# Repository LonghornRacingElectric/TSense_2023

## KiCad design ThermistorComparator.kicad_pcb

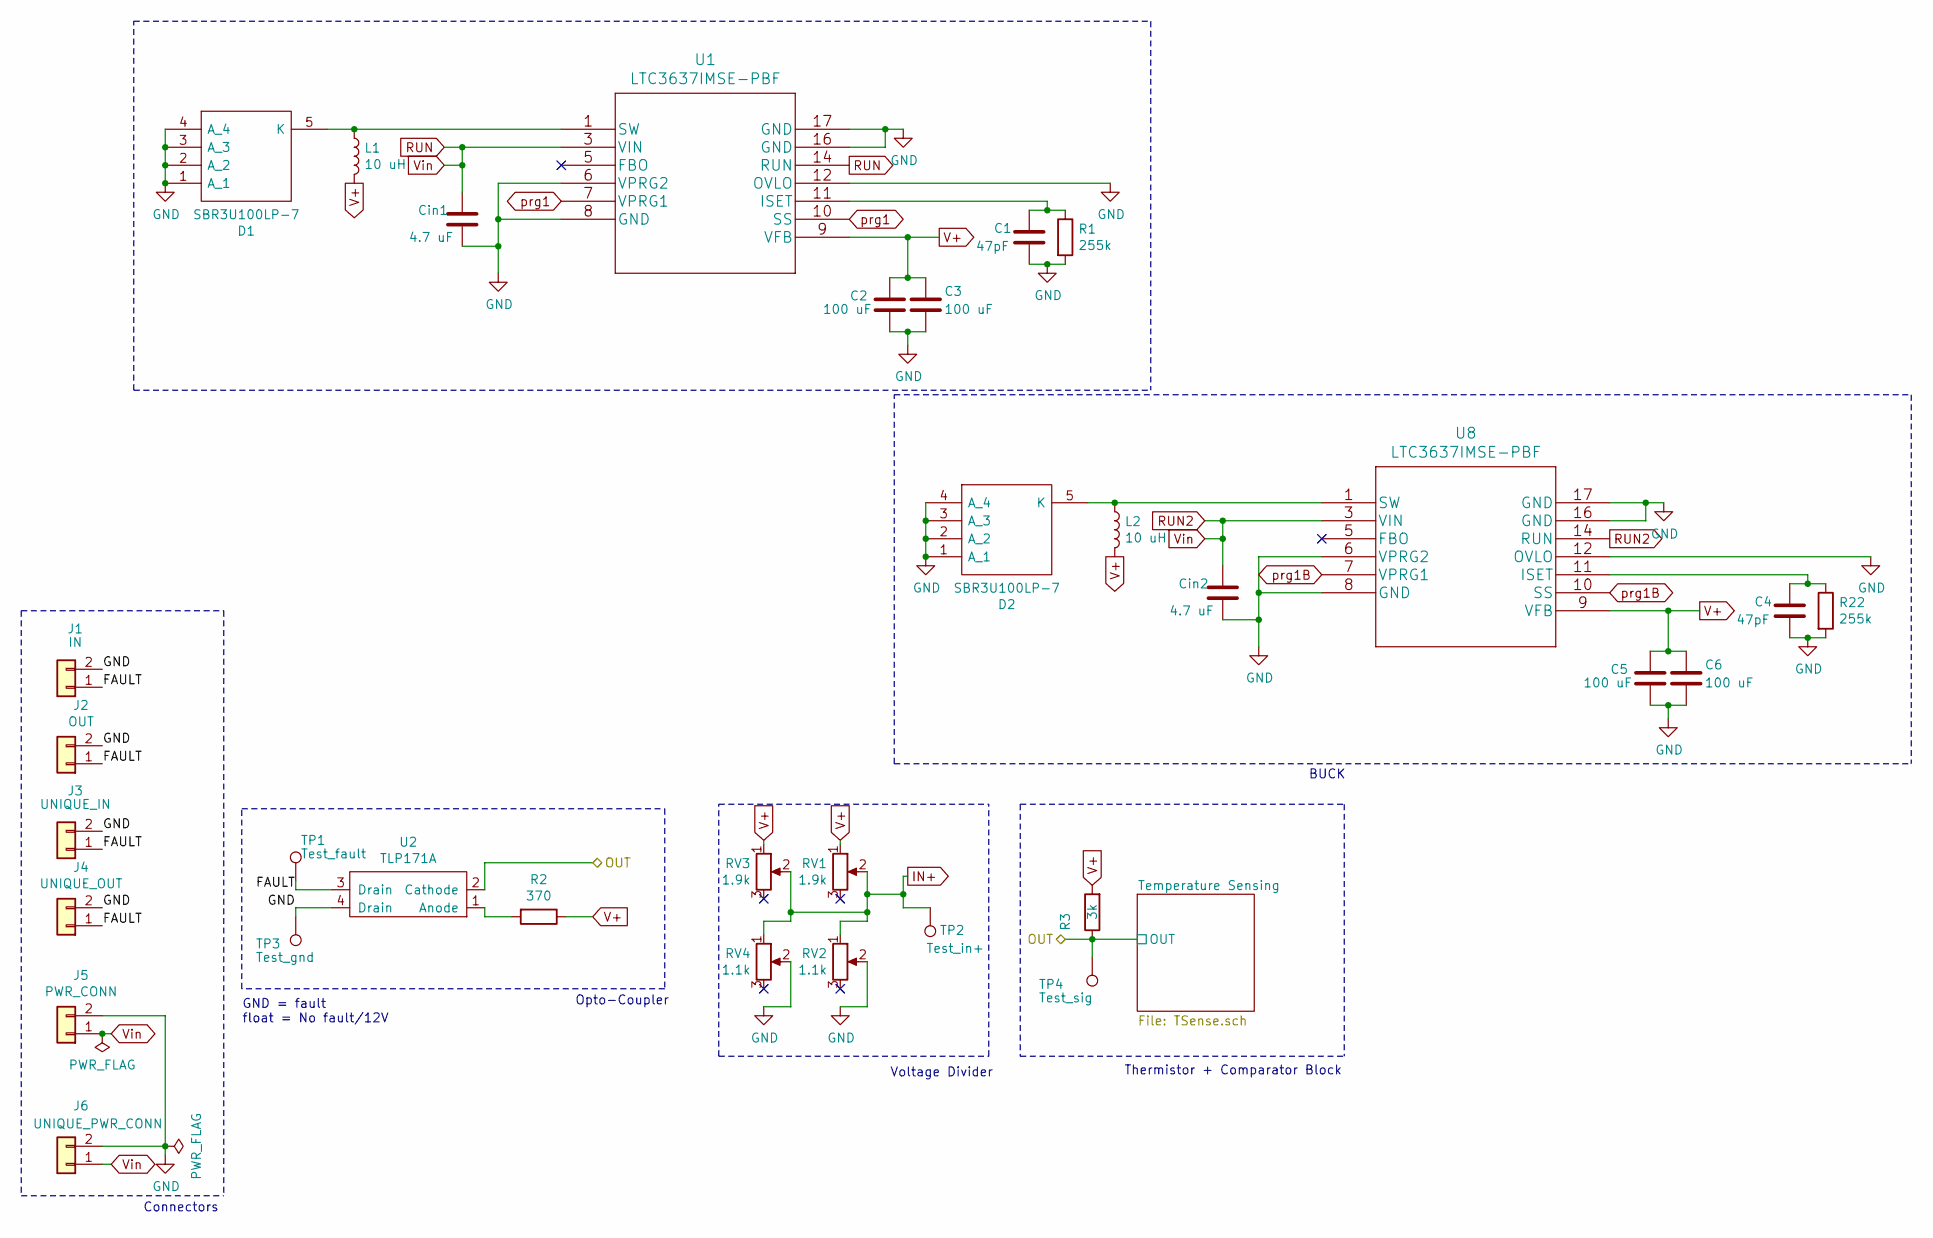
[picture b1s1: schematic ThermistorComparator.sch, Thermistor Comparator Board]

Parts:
C1, C4: 47pF; C_0603_1608Metric_Pad1.08x0.95mm_HandSolder
C2, C3, C5, C6: 100 uF; C_1210_3225Metric_Pad1.33x2.70mm_HandSolder
Cin1, Cin2: 4.7 uF; C_2220_5650Metric_Pad1.97x5.40mm_HandSolder
D1, D2: SBR3U100LP-7; SBR3U100LP7; Manufacturer_Part_Number SBR3U100LP-7; Mouser Part Number 621-SBR3U100LP-7
J1: IN; Molex_Micro-Fit_3.0_43045-0200_2x01_P3.00mm_Horizontal
J2: OUT; Molex_Micro-Fit_3.0_43045-0200_2x01_P3.00mm_Horizontal
J3: UNIQUE_IN; Molex_Micro-Fit_3.0_43045-0210_2x01-1MP_P3.00mm_Horizontal
J4: UNIQUE_OUT; Molex_Micro-Fit_3.0_43045-0210_2x01-1MP_P3.00mm_Horizontal
J5: PWR_CONN; Molex_Micro-Fit_3.0_43045-0200_2x01_P3.00mm_Horizontal
J6: UNIQUE_PWR_CONN; Molex_Micro-Fit_3.0_43045-0210_2x01-1MP_P3.00mm_Horizontal
L1, L2: 10 uH; L_Sumida_CDRH105RNP-100NC
R1, R22: 255k; R_1210_3225Metric_Pad1.30x2.65mm_HandSolder
R2: 370; R_0805_2012Metric_Pad1.20x1.40mm_HandSolder
R3: 3k; R_0805_2012Metric_Pad1.20x1.40mm_HandSolder
RV1, RV3: 1.9k; Potentiometer_Bourns_3299P_Horizontal
RV2, RV4: 1.1k; Potentiometer_Bourns_3299P_Horizontal
TP1: Test_fault; Test_Point_Tiny
TP2: Test_in+; Test_Point_Tiny
TP3: Test_gnd; Test_Point_Tiny
TP4: Test_sig; Test_Point_Tiny
U1, U8: LTC3637IMSE-PBF
U2: TLP171A; SOP-4_3.8x4.1mm_P2.54mm

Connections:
/FAULT: J1.1, J2.1, J3.1, J4.1, TP1.1, U2.3 (Drain)
/OUT: R3.1, TP4.1, U2.2 (Cathode); also elsewhere on the board
GND: C1.2, C2.2, C3.2, C4.2, C5.2, C6.2, Cin1.2, Cin2.2, D1.1 (A_1), D1.2 (A_2), D1.3 (A_3), D1.4 (A_4), D2.1 (A_1), D2.2 (A_2), D2.3 (A_3), D2.4 (A_4), J1.2, J2.2, J3.2, J4.2, J5.2, J6.2, R1.2, R22.2, RV2.2, RV4.2, TP3.1, U1.6 (VPRG2), U1.8 (GND), U1.12 (OVLO), U1.16 (GND), U1.17 (GND), U2.4 (Drain), U8.6 (VPRG2), U8.8 (GND), U8.12 (OVLO), U8.16 (GND), U8.17 (GND); also elsewhere on the board
IN+: RV1.2, RV2.1, RV3.2, RV4.1, TP2.1; also elsewhere on the board
unnamed: C1.1, R1.1, U1.11 (ISET)
unnamed: C4.1, R22.1, U8.11 (ISET)
unnamed: D1.5 (K), L1.1, U1.1 (SW)
unnamed: D2.5 (K), L2.1, U8.1 (SW)
unnamed: R2.2, U2.1 (Anode)
RUN: Cin1.1, Cin2.1, J5.1, J6.1, U1.3 (VIN), U1.14 (RUN), U8.3 (VIN), U8.14 (RUN)
V+: C2.1, C3.1, C5.1, C6.1, L1.2, L2.2, R2.1, R3.2, RV1.1, RV3.1, U1.9 (VFB), U8.9 (VFB); also elsewhere on the board
prg1: U1.7 (VPRG1), U1.10 (SS)
prg1B: U8.7 (VPRG1), U8.10 (SS)

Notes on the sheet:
Voltage Divider
Thermistor + Comparator Block
BUCK
Connectors
Opto-Coupler
GND = fault float = No fault/12V

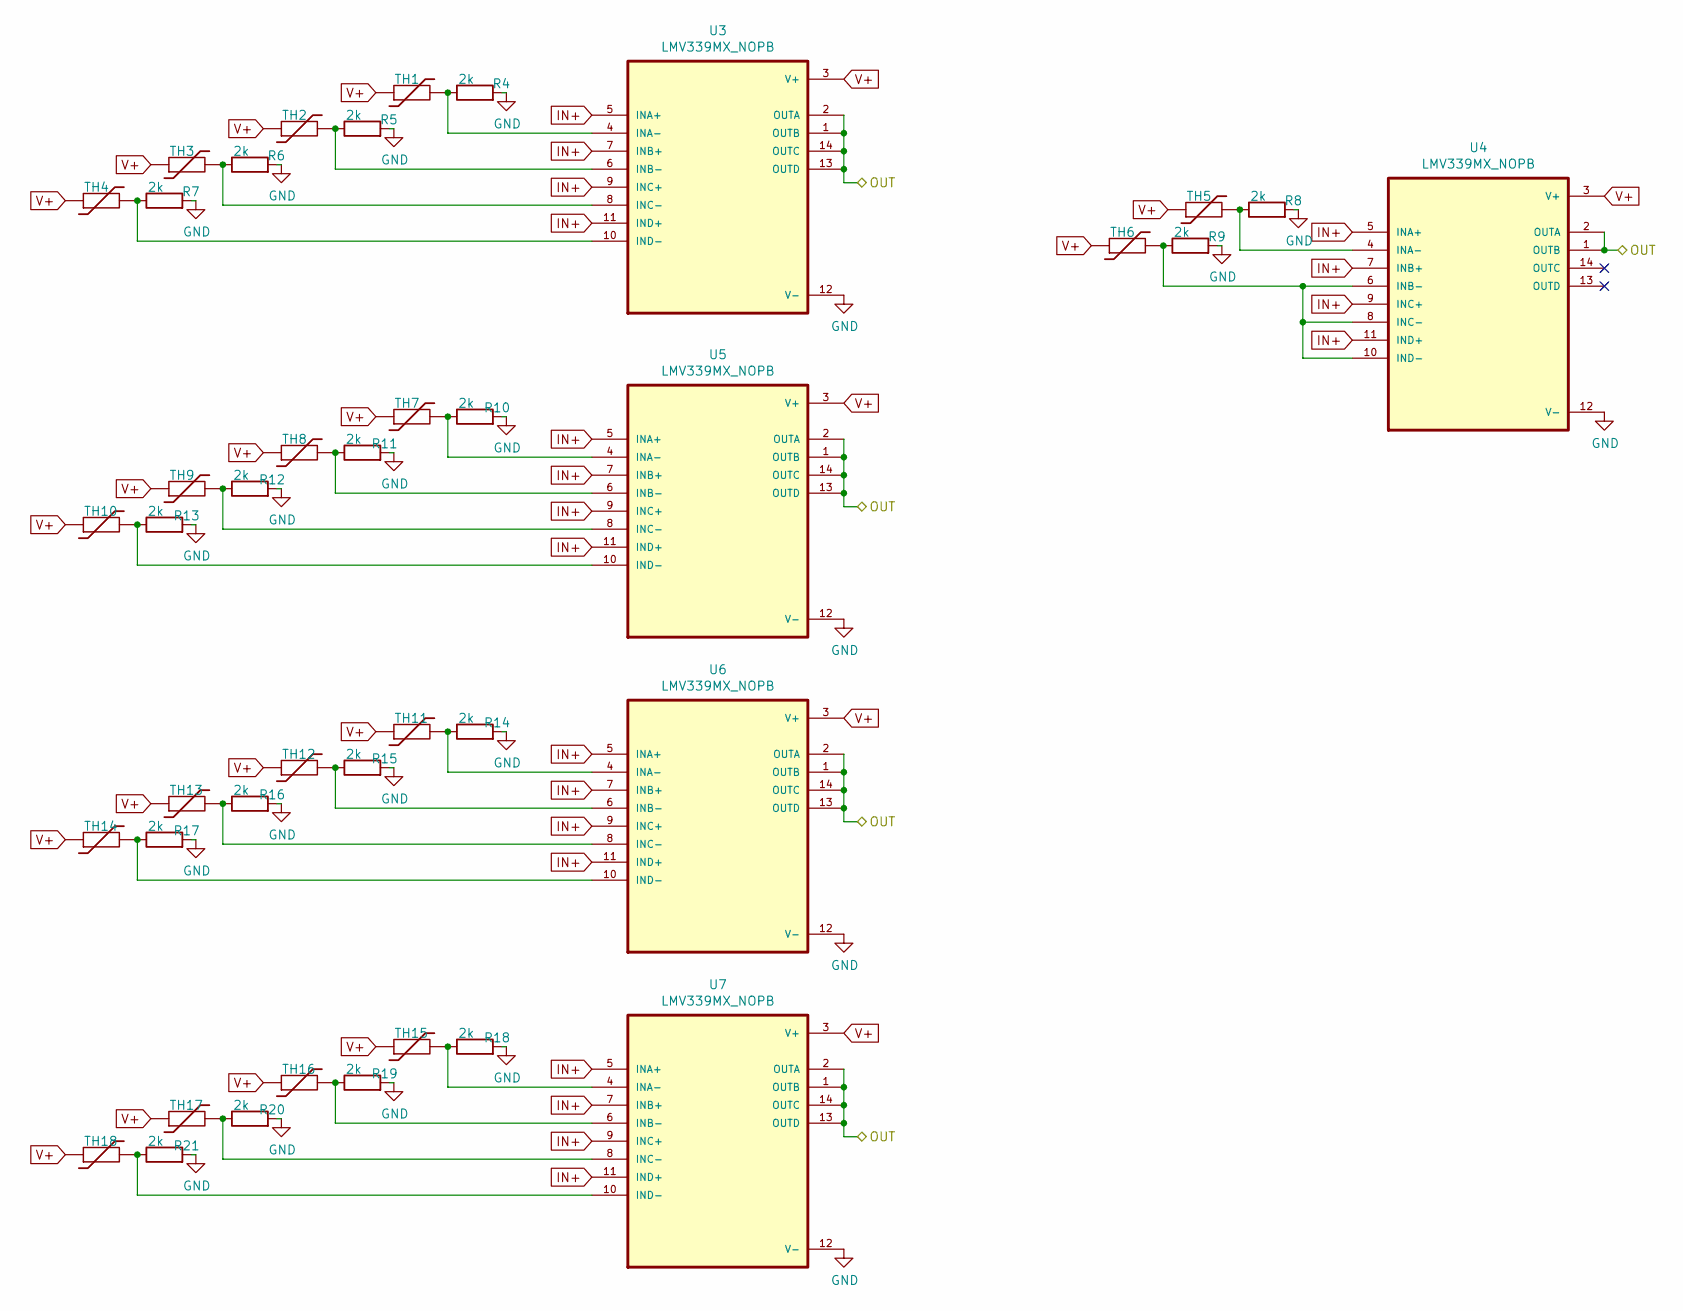
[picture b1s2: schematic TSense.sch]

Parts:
R4, R5, R6, R7, R8, R9, R10, R11, R12, R13, R14, R15, R16, R17, R18, R19, R20, R21: 2k; R_0805_2012Metric_Pad1.20x1.40mm_HandSolder
TH1, TH2, TH3, TH4, TH5, TH6, TH7, TH8, TH9, TH10, TH11, TH12, TH13, TH14, TH15, TH16, TH17, TH18: 1k; R_1206_3216Metric_Pad1.30x1.75mm_HandSolder
U3, U4, U5, U6, U7: LMV339MX_NOPB; SOIC127P600X175-14N

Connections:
/OUT: U3.1 (OUTB), U3.2 (OUTA), U3.13 (OUTD), U3.14 (OUTC), U4.1 (OUTB), U4.2 (OUTA), U5.1 (OUTB), U5.2 (OUTA), U5.13 (OUTD), U5.14 (OUTC), U6.1 (OUTB), U6.2 (OUTA), U6.13 (OUTD), U6.14 (OUTC), U7.1 (OUTB), U7.2 (OUTA), U7.13 (OUTD), U7.14 (OUTC); also elsewhere on the board
GND: R4.2, R5.2, R6.2, R7.2, R8.2, R9.2, R10.2, R11.2, R12.2, R13.2, R14.2, R15.2, R16.2, R17.2, R18.2, R19.2, R20.2, R21.2, U3.12 (V-), U4.12 (V-), U5.12 (V-), U6.12 (V-), U7.12 (V-); also elsewhere on the board
IN+: U3.5 (INA+), U3.7 (INB+), U3.9 (INC+), U3.11 (IND+), U4.5 (INA+), U4.7 (INB+), U4.9 (INC+), U4.11 (IND+), U5.5 (INA+), U5.7 (INB+), U5.9 (INC+), U5.11 (IND+), U6.5 (INA+), U6.7 (INB+), U6.9 (INC+), U6.11 (IND+), U7.5 (INA+), U7.7 (INB+), U7.9 (INC+), U7.11 (IND+); also elsewhere on the board
unnamed: R4.1, TH1.2, U3.4 (INA-)
unnamed: R5.1, TH2.2, U3.6 (INB-)
unnamed: R6.1, TH3.2, U3.8 (INC-)
unnamed: R7.1, TH4.2, U3.10 (IND-)
unnamed: R8.1, TH5.2, U4.4 (INA-)
unnamed: R9.1, TH6.2, U4.6 (INB-), U4.8 (INC-), U4.10 (IND-)
unnamed: R10.1, TH7.2, U5.4 (INA-)
unnamed: R11.1, TH8.2, U5.6 (INB-)
unnamed: R12.1, TH9.2, U5.8 (INC-)
unnamed: R13.1, TH10.2, U5.10 (IND-)
unnamed: R14.1, TH11.2, U6.4 (INA-)
unnamed: R15.1, TH12.2, U6.6 (INB-)
unnamed: R16.1, TH13.2, U6.8 (INC-)
unnamed: R17.1, TH14.2, U6.10 (IND-)
unnamed: R18.1, TH15.2, U7.4 (INA-)
unnamed: R19.1, TH16.2, U7.6 (INB-)
unnamed: R20.1, TH17.2, U7.8 (INC-)
unnamed: R21.1, TH18.2, U7.10 (IND-)
V+: TH1.1, TH2.1, TH3.1, TH4.1, TH5.1, TH6.1, TH7.1, TH8.1, TH9.1, TH10.1, TH11.1, TH12.1, TH13.1, TH14.1, TH15.1, TH16.1, TH17.1, TH18.1, U3.3 (V+), U4.3 (V+), U5.3 (V+), U6.3 (V+), U7.3 (V+); also elsewhere on the board

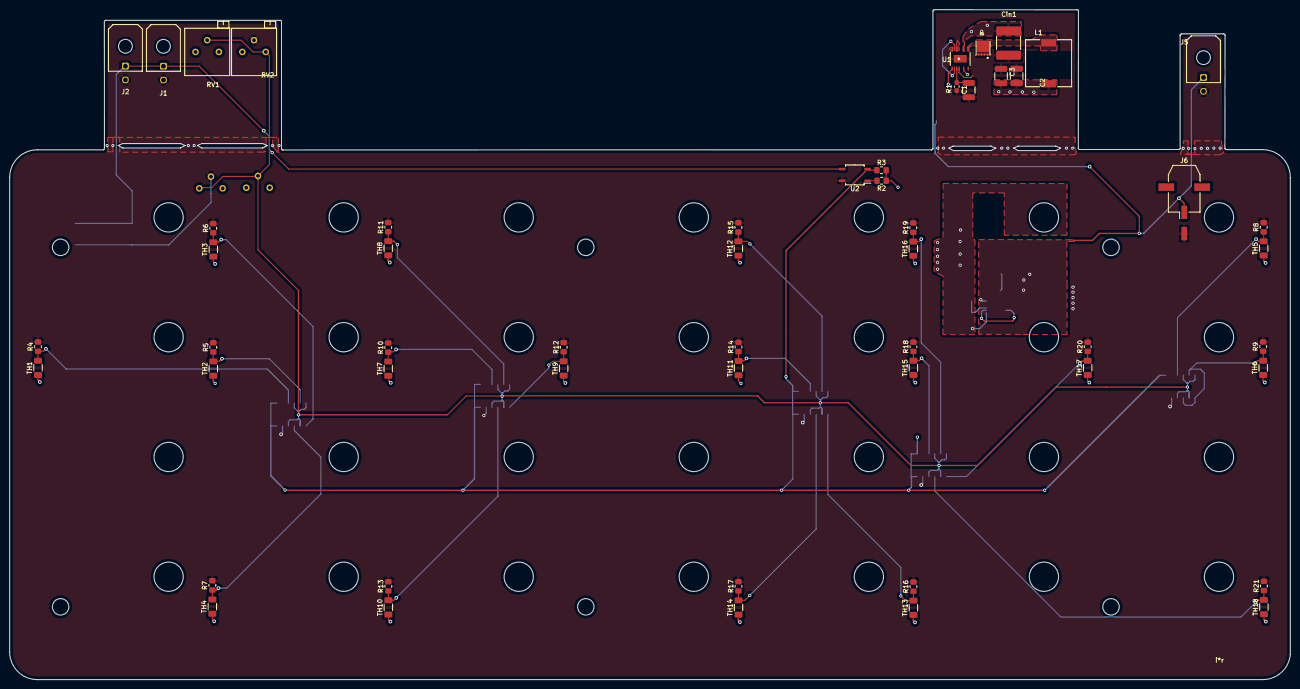
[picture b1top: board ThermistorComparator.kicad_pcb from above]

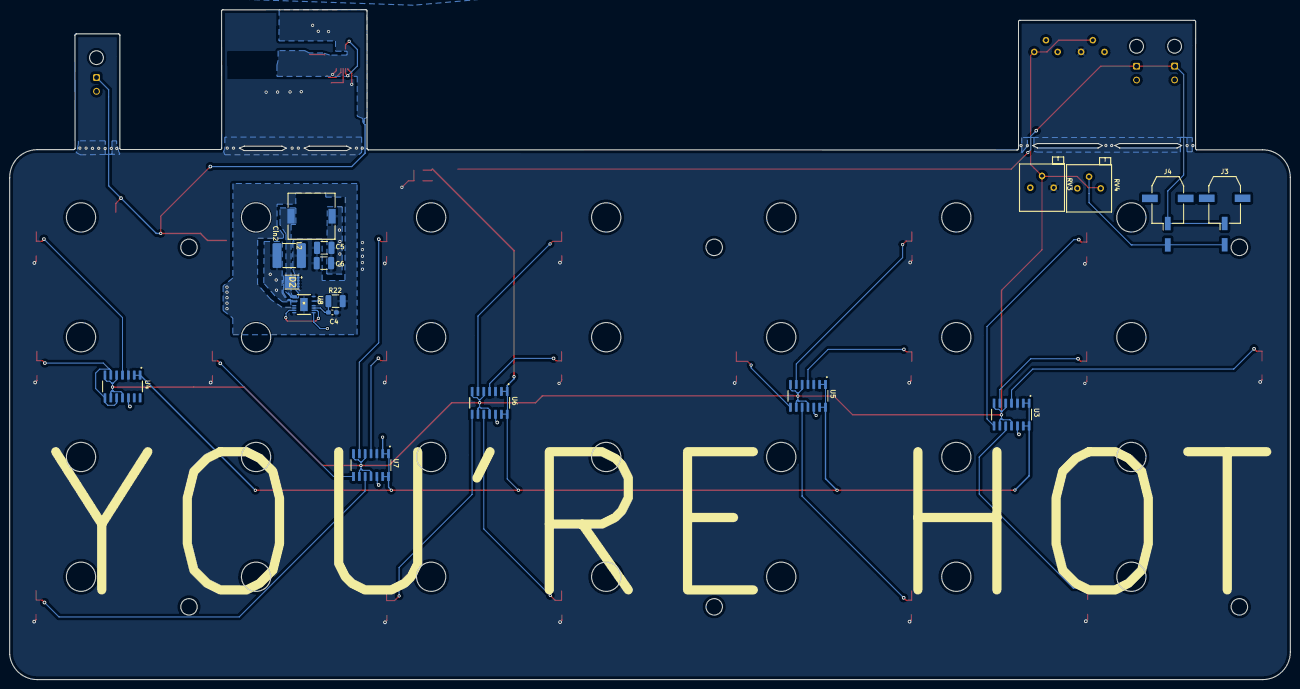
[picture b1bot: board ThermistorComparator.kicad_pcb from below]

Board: 2 copper layers, 278.0 x 145.4 mm, 70 parts (17 on the bottom side), 31 nets.

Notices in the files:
parts and their libraries:
Copyright 2021 Accelerated Designs. All rights reserved.
